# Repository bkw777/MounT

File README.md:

# MounT
Mount a microcontroller dev board onto a "Model T" computer by it's serial port.

This repo has a few different variations of adapter boards to attach some common small DIP form-factor microcontroller boards directly to "Model T" computers by the serial port.

Particularly, boards with integrated SD card readers, for use with [PDDuino](https://github.com/bkw777/PDDuino), but not limited to that.

You can power the microcontroller board from the computer using a [BCR-USB power adapter](https://github.com/bkw777/BCR_Breakout)

These adapter boards take the place of a serial cable, gender/null-modem adapters, RS-232/TTL level-shifter module, and breadboard, and let you stick the whole assembly directly onto the serial port of a TRS-80 Model 100 or any of it's clones.

There are at least a few other machines are not in the same family as above but have the same form of serial port that could also use this:  

And there are also a few other variations for other machines with other serial port configurations.  
Namely one for the Cambridge Z88 and one for a standard 9-pin male PC com port or usb-serial adapter.  
The Cambridge Z88 can use a TPDD drive, and so can use PDDuino, and so has a use for an adapter like this.  
Similarly the TANDY WP-2 can use a TPDD drive, and so has a use for this, and the WP-2 serial port is the same as a standard PC com port.

All of these adapters employ a staggered row footprint for the main pin headers, which acts like a friction fit socket to connect the microcontroller board to the MounT board without having to solder it permanently and without needing actual sockets.  
This way the microcontroller board is still removable like with a socket, yet low profile as if you had soldered it with no sockets.

You can still install real sockets if you want to, or solder the microcontroller board permanently if you want to.

One feature of normal socket headers that can be either good or bad, is they are 8.5mm tall. That makes the controller board stick out more than it needs to, but it also provides a handy space between the microcontroller board and the adapter board where you can stuff a lipo battery, or stuff excess usb cable from the BCR port power adapter.

These adapers (so far), make the following connections between the "Model T" and the microcontroller:
<pre>
Model T              MCU
TX  --> MAX3232 -->  RX  (first/main non-usb hardware serial port RX pin)
RX  <-- MAX3232 <--  TX  (first/main non-usb hardware serial port TX pin)
DTR --> MAX3232 -->  5   (Arduino pin 5)
DSR <-+ MAX3232 <--  6   (Arduino pin 6)
DCD <-+
CTS --- \jumper
RTS --- /
</pre>

## Host Computer Compatibility
### K85 - KC-85 clones, aka "Model T", like TRS-80 Model 100
The source files with "K85" in the name are for the TRS-80 Model 100 and all the other KC-85 clone aka "Model T" machines.  
 TRS-80/TANDY Model 100, 102, 200  
 NEC PC-8201, PC-8201a, PC-8300  
 Olivetti M10  
 Kyotronic KC-85  

Also at least a few other machines are not in that family but have the same serial port configuration and are also compatible with the "K85" versions.  
 NEC PC-8401 "Starlet", PC-8501  
 TANDY 600  

Generically, the serial port of a KC-85 clone is a standard 25-pin DTE port, except that it's a female DB25 instead of male. The "K85" verions of these adapters would be compatible with any machine with that serial port configuration.

### Z88 - Cambridge Z88
Files with "Z88" in the name are for the Cambridge Z88.

The Z88 has a non-standard serial port and so these these are not compatible with anything else but the Z88.

### WP2 - TANDY WP-2
Files with "WP2" in the name are for the TANDY WP-2.

The TANDY WP-2 serial port is also the same as any generic PC 9-pin com port and most usb-serial adapters which are designed to replace legacy motherboard com ports.  
The WP2 versions are also compatible with any other machine with a standard 9-pin DTE male com port.

## Microcontroller Board Compatibility
Files with "Feather" in the name accept any Adafruit Feather form-factor microcontroller board.

Files with "Teensy" in the name accept Teensy 3.5, 3.6, or 4.1 microcontroller boards.

## MounT Adapters
### Adafruit Feather to KC-85 clone / "Model T"

[MounT_K85_Feather PCB from PCBWAY](https://www.pcbway.com/project/shareproject/Feather_MounT.html)  
[MounT_K85_Feather PCB from OSHPark](https://oshpark.com/shared_projects/URa7jGeS)  
[MounT_K85_Feather.BOM.csv](MounT_K85_Feather.BOM.csv) ([DigiKey cart](https://www.digikey.com/short/b35fdb5b))

Adafruit Feather boards are the ideal for this.  
* The pin rows are assymetrical, and so the board as a whole has polarity protection. You physically can't plug it in backwards or upside-down or any way but the correct way.  
* The boards all have built-in lipo battery chargers, JST connectors for lipo cells, and an Enable pin that allows an add-on board like MounT to provide an on/off switch without needing to unplug the battery or hack a switch in series between the battery and the Feather board.  
* There are many different microcontroller boards that all conform to the same physical and electrical pinout standard, and can all be used with this.

Adafruit Feather Adalogger boards can be powered by a lipo battery instead of, or as well as, the BCR port adapter (or other usb power source).  
The Feather board includes both a JST connector for a lipo cell, and an on-board lipo cell manager so that it charges when you supply power to the usb port, and provides power when there is no power from the usb port.

Avoid connecting a battery and the BCR port adapter at the same time. The charging circuit on the Feather board will try to charge the battery at 100ma any time there is power available from the usb port. But that is too much current to draw from the BCR port. So, either connect a battery, OR the BCR port adapter, not both at the same time.  
If you are going to use a battery, you can charge it by just connecting any usb power source (except the BCR port adapter) to the usb port.

There are many Adafruit Feather boards, and they would all work with this. But for PDDuino you want either Adalogger 32u4 or Adalogger M0 because they have built-in sd card readers.  
M0 has a newer more powerful cpu and more ram, but is actually a bit less reliable due to some problem with the Adafruit board support library. There is a known problem with the SPI timing, which apparently was a deliberate choice by Adafruit to get more performance for audio applications at the expense of stability.  
32u4 is an older and less powerful cpu, and has less flash and less ram, but it actually works perfect for PDDuino and the Adalogger 32u4 really the ideal board for PDDuino.  
Other Feather boards could possibly be used for wifi/rf or general use, but they don't have sd card readers built-in, so they aren't as useful for PDDuino.

### Teensy 3.5/3.6/4.1 to KC-85 clone / "Model T"

[MounT_K85_Teensy PCB from PCBWAY](https://www.pcbway.com/project/shareproject/Teensy_MounT_32836e10.html)  
[MounT_K85_Teensy PCB from OSHPark](https://oshpark.com/shared_projects/XVh5R6QG)  
[MounT_K85_Teensy.BOM.csv](MounT_K85_Teensy.BOM.csv) ([DigiKey cart](https://www.digikey.com/short/fwzdd8v9))

The Teensy 3.5 specifically is particularly interesting for vintage computer projects as it's i/o pins are 5v tolerant. Though this isn't needed   
The Teensy 3.5/3.6/4.1 are far more powerful and have far more built-in hardware & features, but do have a few downsides compared to Feather.  
The pins are physically symmetrical, which means there is no polarity protection. It's always possible to plug the teensy in backwards.  
The Teensy does not have a built-in lipo charger and connector. It can run off the BCR port, but it would take more added hardware to run off a battery, and even more to have that battery be automatically charged from the usb port.  
The Teensy does not have any pins wired up to the card-detect pin in the sd card reader. This means the arduino code can not automatically detect when the card is ejected. This means PDDuino can't automatically reset and return to "waiting-for-card" state the way Feather can and does. The card slot does have a sense switch, so you could manually solder connections to it and uncomment a few lines in the code to use it.  

## Adafruit Feather to TANDY WP-2 and/or generic PC

<!-- [MounT_WP2_Feather PCB from OSHPark](https://oshpark.com/shared_projects/67NyaQRs)  -->
[MounT_WP2_Feather.BOM.csv](MounT_WP2_Feather.BOM.csv) ([DigiKey cart](https://www.digikey.com/short/tnb09np7))

## Adafruit Feather to Cambridge Z88

<!-- [MounT_Z88_Feather PCB from OSHPark](https://oshpark.com/shared_projects/JzfpyaOQ)  -->
[MounT_Z88_Feather.BOM.csv](MounT_Z88_Feather.BOM.csv) ([DigiKey cart](https://www.digikey.com/short/80rf2r75))

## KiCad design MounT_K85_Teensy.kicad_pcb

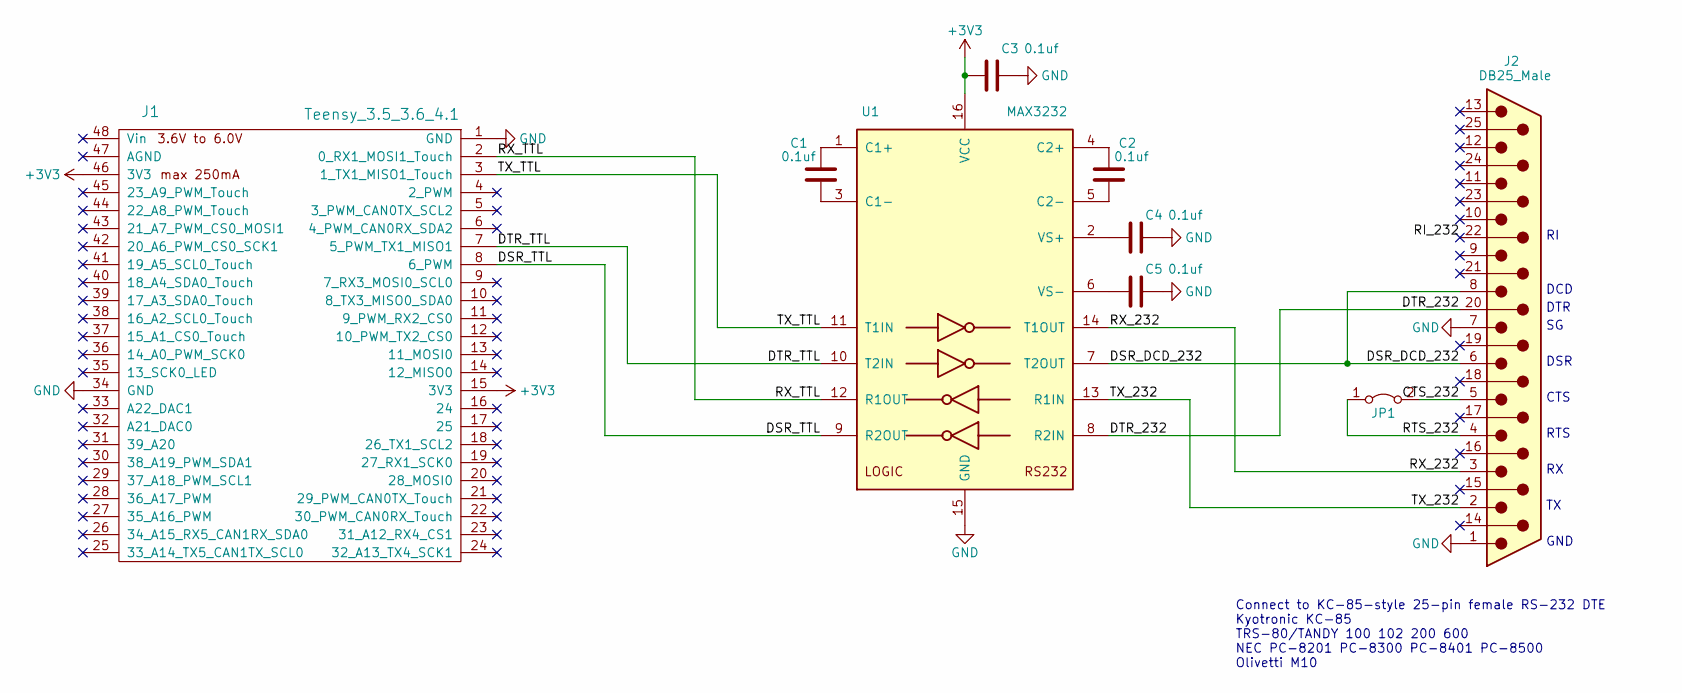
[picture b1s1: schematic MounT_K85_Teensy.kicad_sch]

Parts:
C1, C2, C3, C4, C5: 0.1uf; C_0805
J1: Teensy_3.5_3.6_4.1; Teensy_3.5_3.6_4.1_DIP_friction
J2: DB25_Male; DSUB-25_Male_Vertical_P2.77x2.84mm
JP1: Jumper_2_Bridged; PinHeader_1x02_P2.54mm_Horizontal
U1: MAX3232; SOIC-16_W3.90mm

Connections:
+3V3: C3.1, J1.15 (3V3), J1.46 (3V3), U1.16 (VCC)
/CTS_232: J2.5, JP1.2 (B)
/DSR_DCD_232: J2.6, J2.8, U1.7 (T2OUT)
/DSR_TTL: J1.8 (6_PWM), U1.9 (R2OUT)
/DTR_232: J2.20, U1.8 (R2IN)
/DTR_TTL: J1.7 (5_PWM_TX1_MISO1), U1.10 (T2IN)
/RI_232: J2.22
/RTS_232: J2.4, JP1.1 (A)
/RX_232: J2.3, U1.14 (T1OUT)
/RX_TTL: J1.2 (0_RX1_MOSI1_Touch), U1.12 (R1OUT)
/TX_232: J2.2, U1.13 (R1IN)
/TX_TTL: J1.3 (1_TX1_MISO1_Touch), U1.11 (T1IN)
GND: C3.2, C4.2, C5.2, J1.1 (GND), J1.34 (GND), J2.1, J2.7, U1.15 (GND)
unnamed: C1.1, U1.1 (C1+)
unnamed: C1.2, U1.3 (C1-)
unnamed: C2.1, U1.4 (C2+)
unnamed: C2.2, U1.5 (C2-)
unnamed: C4.1, U1.2 (VS+)
unnamed: C5.1, U1.6 (VS-)

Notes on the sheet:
DTR
Connect to KC-85-style 25-pin female RS-232 DTE Kyotronic KC-85 TRS-80/TANDY 100 102 200 600 NEC PC-8201 PC-8300 PC-8401 PC-8500 Olivetti M10
DSR
GND
DCD
RTS
CTS

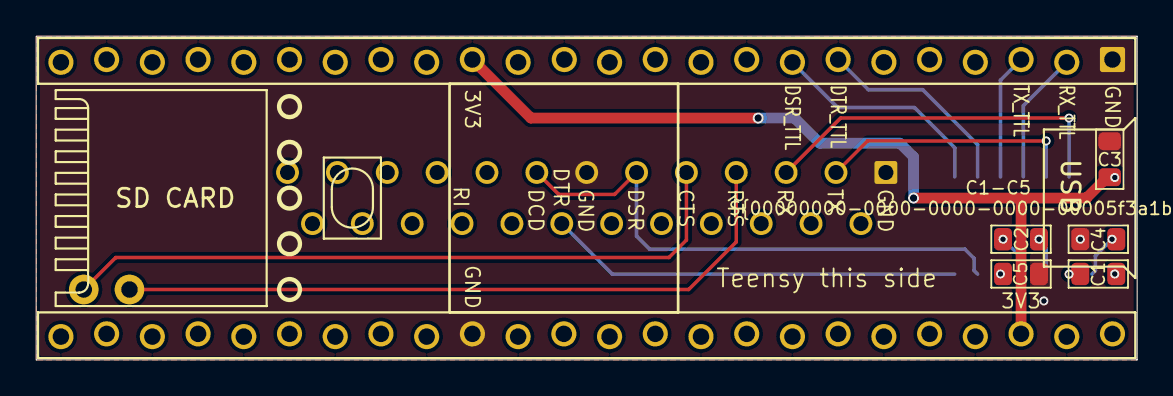
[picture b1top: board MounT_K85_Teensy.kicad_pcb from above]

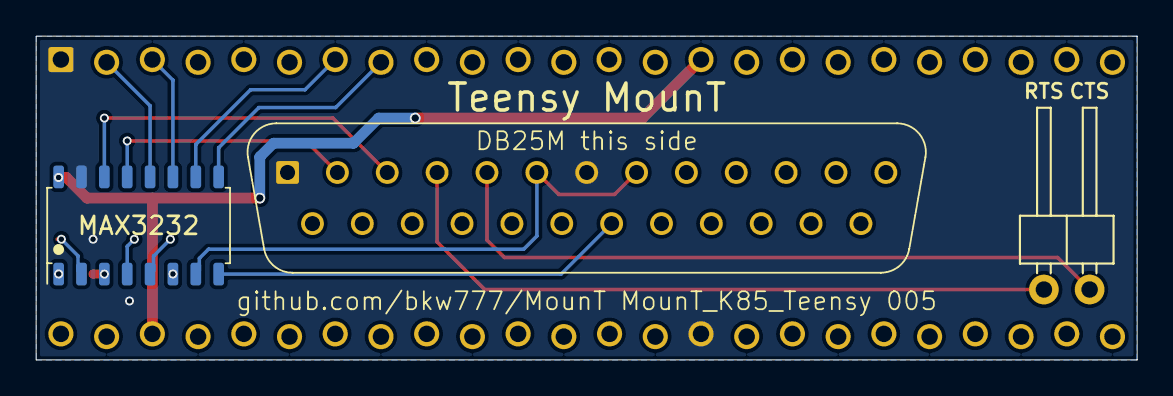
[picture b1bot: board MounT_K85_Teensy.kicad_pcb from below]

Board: 2 copper layers, 61.2 x 18.0 mm, 9 parts (3 on the bottom side), 18 nets.

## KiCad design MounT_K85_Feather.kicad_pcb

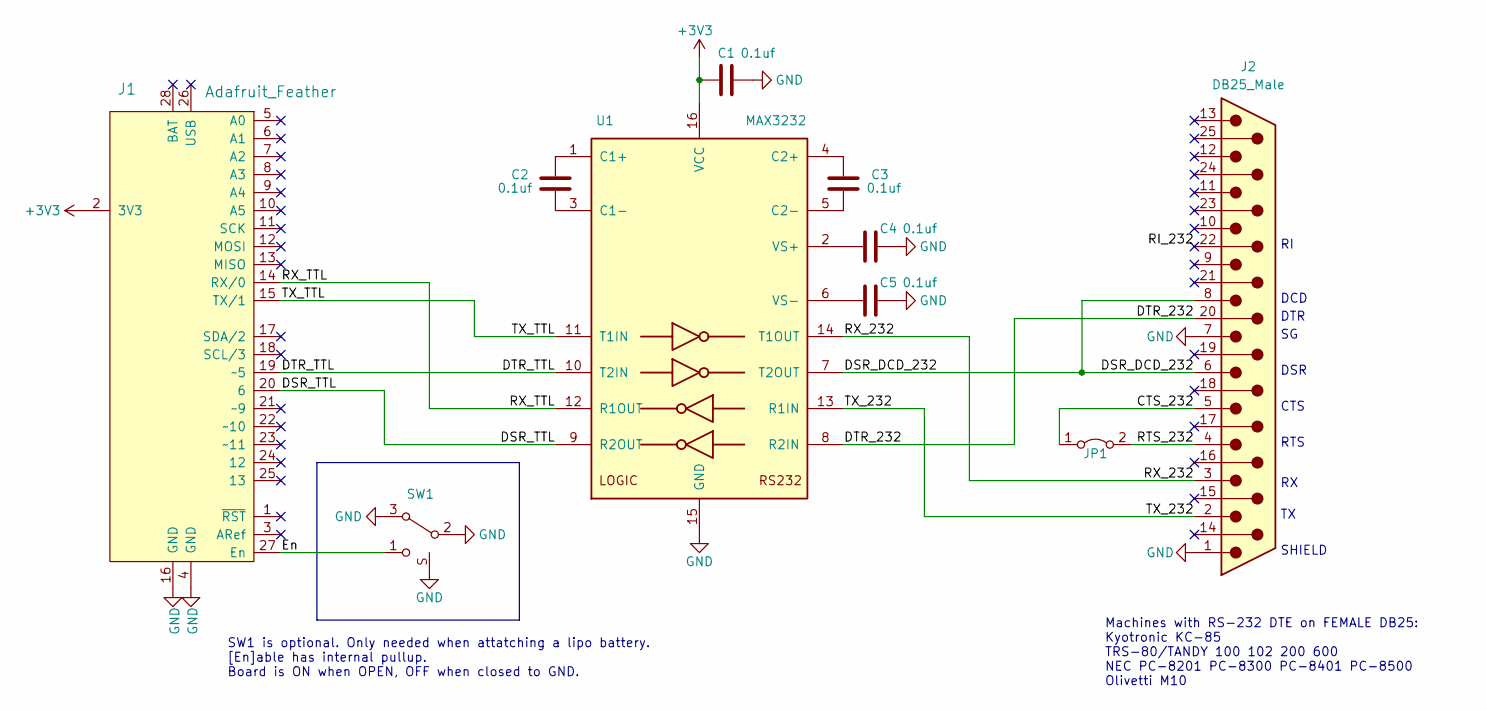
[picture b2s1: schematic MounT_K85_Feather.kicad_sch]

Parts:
C1, C2, C3, C4, C5: 0.1uf; C_0805
J1: Adafruit_Feather; Adafruit_Feather_stagger_6mil
J2: DB25_Male; DSUB-25_Male_Vertical_P2.77x2.84mm
JP1: Jumper_2_Bridged; PinHeader_1x02_P2.54mm_Horizontal
SW1: CUS-12TB; EG1215
U1: MAX3232; SOIC-16_W3.90mm

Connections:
+3V3: C1.1, J1.2 (3V3), U1.16 (VCC)
/CTS_232: J2.5, JP1.1 (A)
/DSR_DCD_232: J2.6, J2.8, U1.7 (T2OUT)
/DSR_TTL: J1.20 (6), U1.9 (R2OUT)
/DTR_232: J2.20, U1.8 (R2IN)
/DTR_TTL: J1.19 (~5), U1.10 (T2IN)
/En: J1.27 (En), SW1.1
/RI_232: J2.22
/RTS_232: J2.4, JP1.2 (B)
/RX_232: J2.3, U1.14 (T1OUT)
/RX_TTL: J1.14 (RX/0), U1.12 (R1OUT)
/TX_232: J2.2, U1.13 (R1IN)
/TX_TTL: J1.15 (TX/1), U1.11 (T1IN)
GND: C1.2, C4.2, C5.2, J1.4 (GND), J1.16 (GND), J2.1, J2.7, SW1.2 (Common), SW1.3, SW1.S (Shell), U1.15 (GND)
unnamed: C2.1, U1.1 (C1+)
unnamed: C2.2, U1.3 (C1-)
unnamed: C3.1, U1.4 (C2+)
unnamed: C3.2, U1.5 (C2-)
unnamed: C4.1, U1.2 (VS+)
unnamed: C5.1, U1.6 (VS-)

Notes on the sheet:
SW1 is optional. Only needed when attatching a lipo battery. [En]able has internal pullup. Board is ON when OPEN, OFF when closed to GND.
DCD
RTS
Machines with RS-232 DTE on FEMALE DB25: Kyotronic KC-85 TRS-80/TANDY 100 102 200 600 NEC PC-8201 PC-8300 PC-8401 PC-8500 Olivetti M10
SHIELD
CTS
DSR
DTR

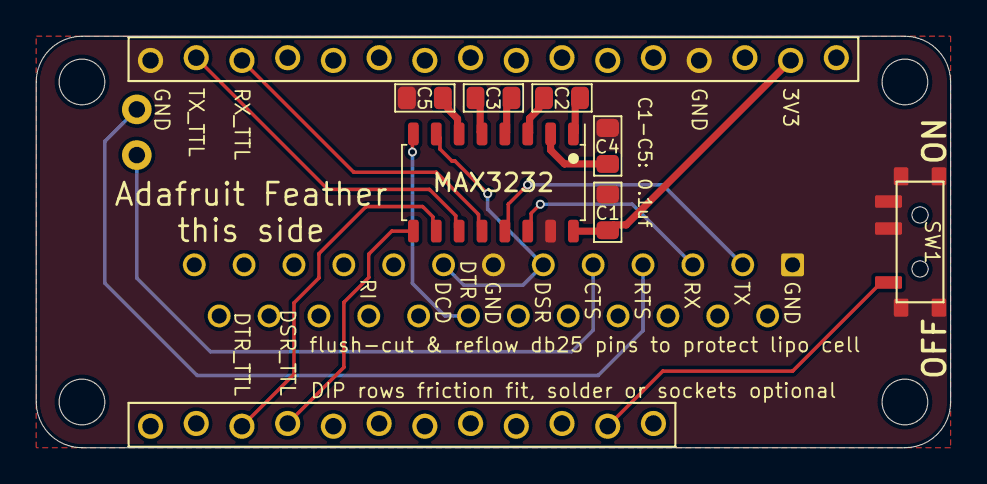
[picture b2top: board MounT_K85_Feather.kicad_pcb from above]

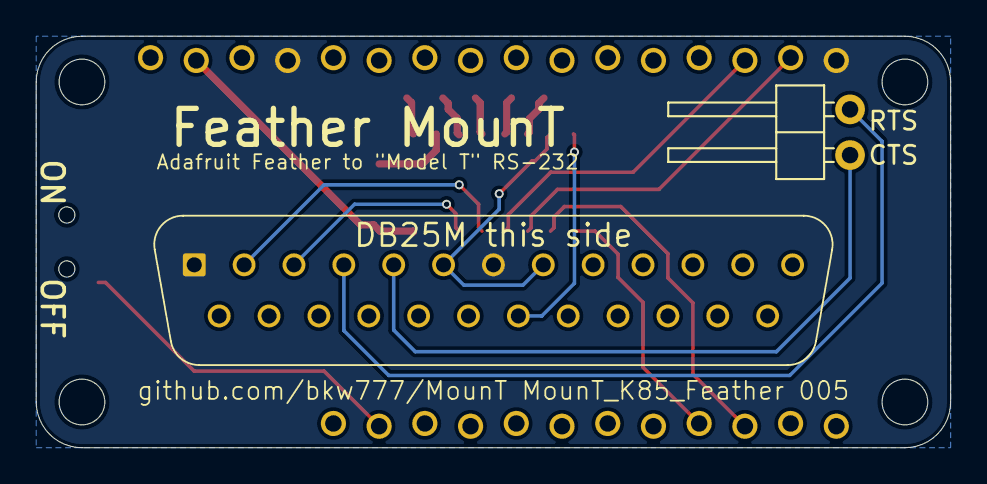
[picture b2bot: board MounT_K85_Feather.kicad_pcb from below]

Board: 2 copper layers, 50.8 x 22.9 mm, 10 parts (2 on the bottom side), 19 nets.

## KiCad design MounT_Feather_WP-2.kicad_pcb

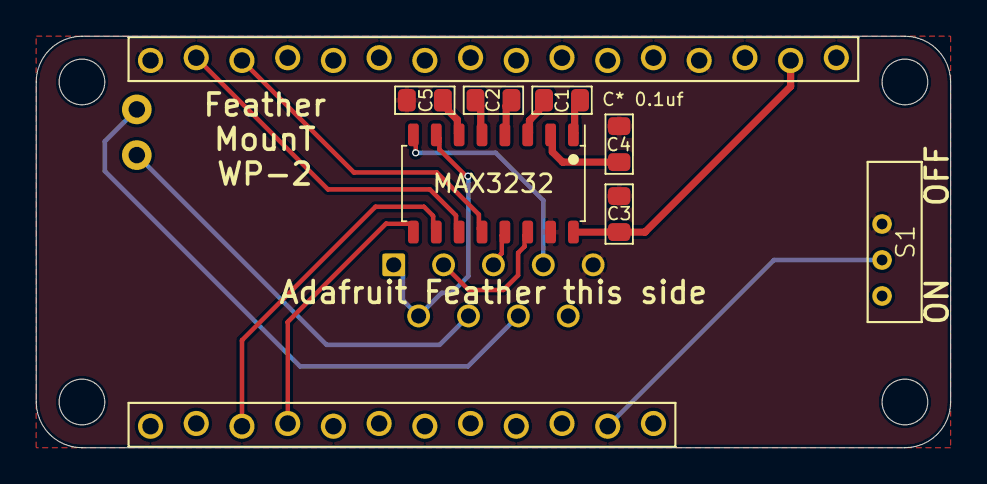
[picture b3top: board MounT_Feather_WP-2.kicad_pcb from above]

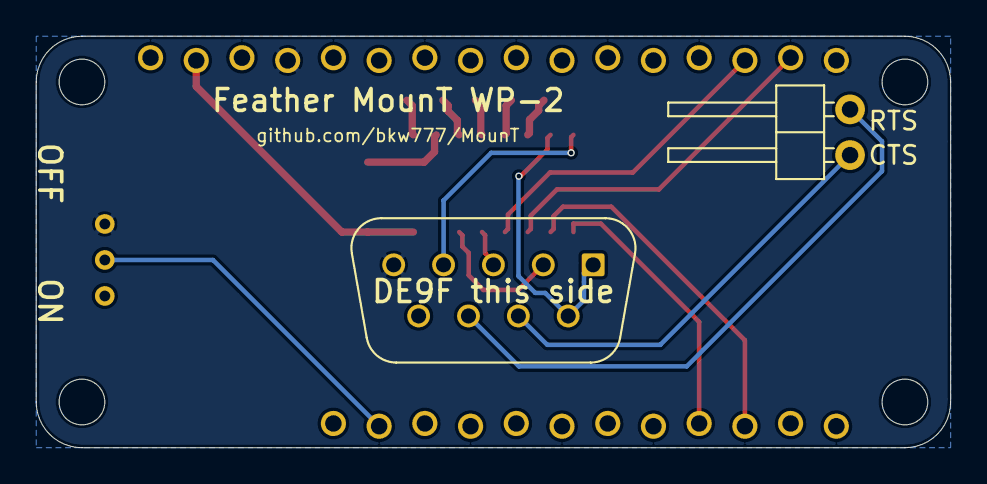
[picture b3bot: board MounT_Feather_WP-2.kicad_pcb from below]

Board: 2 copper layers, 50.8 x 22.9 mm, 11 parts (3 on the bottom side), 20 nets.

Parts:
C1, C2, C3, C4, C5: 0.1uf; C_0805
J1: Adafruit_Feather; Adafruit_Feather_stagger_6mil
J2: DE9_Female; DSUB-9_Female_Vertical_P2.77x2.84mm
JP1: Jumper_2_Bridged; PinHeader_1x02_P2.54mm_Horizontal
NT1: Net-Tie_2; NetTie-2_SMD_10
S1: DS04-254-1L-01BK; CSS-121xC
U1: MAX3232; SOIC-16_W3.90mm

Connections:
+3V3: C3.1, J1.2, U1.16
/CTS_232: J2.8, JP1.2
/DCD_232: J2.1, NT1.2
/DSR_232: J2.6, NT1.1, U1.7
/DSR_TTL: J1.20, U1.9
/DTR_232: J2.4, U1.8
/DTR_TTL: J1.19, U1.10
/En: J1.27, S1.2
/RTS_232: J2.7, JP1.1
/RX_232: J2.2, U1.14
/RX_TTL: J1.14, U1.12
/TX_232: J2.3, U1.13
/TX_TTL: J1.15, U1.11
GND: C3.2, C4.2, C5.2, J1.4, J1.16, J2.5, S1.3, U1.15
unnamed: C1.1, U1.1
unnamed: C1.2, U1.3
unnamed: C2.1, U1.4
unnamed: C2.2, U1.5
unnamed: C4.1, U1.2
unnamed: C5.1, U1.6

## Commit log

2020-08-19 initial
2020-08-19 DSR_TTL pulldown
2020-08-20 silkscreen & bom
2020-08-20 alternate routing
2020-08-22 Teensy
2020-08-22 Link for Teensy pcb
2020-08-22 teensy renders
2020-08-26 boms and remove dsr pulldown
2020-08-26 remove dsr pulldown
2020-08-27 remove unneeded dsr pulldowns, stagger pin rows
2020-08-28 remove unused models, update readme
2020-08-28 readme
2020-08-31 readme and hardware_notes.txt
2020-08-31 Teensy BOM missing jumper
2020-08-31 add svg schematics in readme
2020-09-05 reduce pin stagger offset from 12 mils to 8 mils
2020-09-05 opdate oshpark links
2020-09-07 add Z88 version for Adafruit Feather
2020-09-17 reduce pin stagger offset to 4mil
2020-09-20 add Feather MounT WP-2
2020-09-22 de9f model, update renders
2020-09-22 update feather z88 footprint & renders
2020-09-29 WP2 & Z88, move DE9 shell away from pins. Increase solder pads in S1.
2020-09-29 update oshpark links
2020-10-02 use 6mil stagger, 4mil wasn't good enough
2021-03-06 fix pin locations in feather stagger 6mil footprint
2021-03-06 update oshpark pcb links that use feather stagger 6mil footprint
2021-03-07 Increase minimum drill size to 0.3mm on Feather MounT to make PCBWAY a lot cheaper
2021-03-07 touch up render
2021-03-31 nothing really
2022-01-15 mostly just readme & link to pcbway
2022-09-22 sch plot
2022-10-24 smt power switch, silkscreens, teensy symbol, file/title/revision names
2022-10-25 smt power switch on feather, routing 3v3 on teensy, silkscreen all

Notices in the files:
MounT_K85_Teensy.kicad_pcb:
CC-BY-SA
